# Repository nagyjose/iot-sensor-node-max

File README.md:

# IoT Sensor Node Max (`iot-sensor-node-max`)

> Full-featured wireless IoT environmental & telemetry node based on the Raspberry Pi Pico W, equipped with dual 18650 Li-Ion batteries, independent dual-channel charging & protection, zero-quiescent voltage sensing, multiple sensor interfaces, rich expansion ports (dual I2C, dual SPI, analog ADC), and complete production-ready CAM Gerber data.

**Project Status:** Completed & Functional | **Technologies:** Autodesk Eagle, Hardware PCB Design, RP2040 / Pico W, RS-274X Gerbers, MicroPython / C++

---

## 1. Overview & Key Features

The **IoT Sensor Node Max** is the high-capacity, expandable flagship hardware revision in the Raspberry Pi Pico W sensor node family. Designed for remote deployments where long battery autonomy and extensive sensor connectivity are vital, it doubles the battery capacity with two 18650 cells, provides independent per-cell safety and charging circuits, and breaks out dual I2C, dual SPI, analog ADC, and multi-purpose GPIO expansion headers.

### Key Highlights
- **Microcontroller:** Raspberry Pi Pico W socket (RP2040 dual-core ARM Cortex-M0+ up to 133 MHz, 264 KB SRAM, 2 MB Flash, onboard 2.4 GHz 802.11n Wi-Fi and BLE 5.2).
- **Dual-Cell Power Architecture:**
  - Dual 18650 Li-Ion battery holders (`BAT1` & `BAT2`) with parallel power path configuration for doubled battery operating life.
  - **Dual Microchip MCP73831T** linear Li-Ion charge controllers (`U1`, `U3`) with independent charging status LEDs (`D1`, `D2`), charging both cells in parallel via USB VBUS.
  - **Dual Diodes Inc. AP9101C** dedicated protection ICs (`U2`, `U4`) paired with dual **BXT280N02B** N-MOSFETs (`M1`, `M2`) providing independent overcharge, overdischarge cutoff, and short-circuit protection for each individual cell.
  - **Triple Power Path Switch:** Schottky diode array (`STPS1L30`) and P-channel power MOSFET (`YJL2301D`, `M3`) for seamless automatic handover between external USB 5 V and battery rails.
- **Dual-Channel Precision Battery Monitoring:**
  - **LM4040** precision shunt voltage reference tied to RP2040 `ADC_REF`.
  - Independent switched resistor dividers for each battery cell:
    - Cell 1: Switched by GP3 (`EN-MEAS-1`) via MOSFETs `M4` & `M6` into `VADC-1` (`GP27`).
    - Cell 2: Switched by GP2 (`EN-MEAS-0`) via MOSFETs `M4` & `M5` into `VADC-2` (`GP28`).
  - Zero quiescent current draw through measurement dividers during sleep mode.
  - Diode clamping protection (`RB751V40T1G`) across all ADC inputs.
- **Integrated Sensors & Displays:**
  - **AM2302 (DHT22):** Relative humidity and ambient temperature digital sensor on `GP14`.
  - **DS18B20:** 1-Wire precision digital temperature sensor on `GP15`.
  - **OLED Display Header:** 4-pin socket for 0.96" or 1.3" I2C OLED displays (SSD1306 / SH1106) on `I2C0` (`GP4` / `GP5`).
  - **nRF24L01+ 2.4 GHz RF Header:** SPI socket for Nordic nRF24L01+ wireless transceiver module on `SPI0` (`GP16`–`GP20`).
- **Rich Expansion Connectors:**
  - **Dual I2C Connectors (`CON3`, `CON4`):** 4-pin headers for external I2C sensor daisy chains (BME280, SHT31, INA219, etc.).
  - **Dual SPI Connectors (`CON5`, `CON6`):** 5-pin headers with dedicated independent Chip Selects `CSN-1` (`GP21`) and `CSN-2` (`GP22`).
  - **External Analog Input (`CON1`):** 3-pin connector (VCC, GND, SIG) on `GP26` with Schottky overvoltage clamping for analog sensors.
  - **S2G6 Jumper / Breakout (`CON7`):** Multi-purpose configuration jumper matrix breaking out digital GPIOs `GP6`–`GP13`.
- **Complete Manufacturing Package:** Includes verified RS-274X Gerbers, NC drill files, automated Pick & Place (PnP) centroid files, and pre-packaged ZIP archives ready for PCB manufacturing (JLCPCB, PCBWay).

---

## 2. Architecture & Block Diagram

```mermaid
flowchart TD
    subgraph PowerSystem["⚡ Dual Battery Power & Protection System"]
        USB["USB 5V (VBUS)"] --> CHG1["MCP73831T Charger 1<br/>+ LED D1"]
        USB --> CHG2["MCP73831T Charger 2<br/>+ LED D2"]
        USB --> PATH["Power Path Switch<br/>(P-MOS M3 & D3)"]
        BAT1["18650 Battery Cell 1"] --> PROT1["AP9101C + Dual NMOS M1<br/>Protection Circuit"]
        BAT2["18650 Battery Cell 2"] --> PROT2["AP9101C + Dual NMOS M2<br/>Protection Circuit"]
        CHG1 --> PROT1
        CHG2 --> PROT2
        PROT1 -->|D4 Schottky| PATH
        PROT2 -->|D5 Schottky| PATH
        PATH --> VSYS["VSYS (System Rail)"]
        VSYS --> PICO_REG["Pico W RT6154<br/>Buck-Boost Converter"]
        PICO_REG --> 3V3["3.3V Power Rail"]
    end

    subgraph DualMonitoring["🔋 Independent Battery Telemetry"]
        PROT1 -->|VBATT-1| DIV1["Switched Divider 1<br/>(8.2k / 22k)"]
        PROT2 -->|VBATT-2| DIV2["Switched Divider 2<br/>(8.2k / 22k)"]
        MCU -->|GP3: EN-MEAS-1| GATE1["MOSFET Gate M4 / M6"]
        MCU -->|GP2: EN-MEAS-0| GATE2["MOSFET Gate M4 / M5"]
        GATE1 --> DIV1
        GATE2 --> DIV2
        DIV1 -->|VADC-1| ADC1["ADC1 (GP27) - Cell 1"]
        DIV2 -->|VADC-2| ADC2["ADC2 (GP28) - Cell 2"]
        VREF["LM4040 Precision Ref"] -->|ADC_REF| PICO
    end

    subgraph MCU["🧠 Processing & Core Connectivity"]
        PICO["Raspberry Pi Pico W<br/>(RP2040 MCU)"]
        WIFI["Onboard CYW43439<br/>Wi-Fi 802.11n & BLE 5.2"]
    end

    subgraph IntegratedPeripherals["📡 Onboard Sensors & Radio"]
        DHT["AM2302 / DHT22<br/>(Humidity & Temp)"] ---|GP14| MCU
        DS["DS18B20<br/>(1-Wire Temp)"] ---|GP15| MCU
        OLED["OLED Display<br/>(SSD1306 / SH1106)"] ---|I2C0: GP4/GP5| MCU
        NRF["nRF24L01+ Module<br/>(2.4 GHz RF)"] ---|SPI0: GP16-GP20| MCU
    end

    subgraph ExpansionBuses["🔌 Expansion Ports"]
        I2C_EXT["Dual I2C Expansion<br/>(CON3 & CON4)"] ---|I2C0 Bus| MCU
        SPI_EXT["Dual SPI Expansion<br/>(CON5: CS1 / CON6: CS2)"] ---|SPI0 + GP21/GP22| MCU
        ADC_EXT["External ADC Sensor<br/>(CON1 - Protected)"] ---|GP26: VADC-0| MCU
        JUMP["Jumper / GPIO Breakout<br/>(CON7: S2G6)"] ---|GP6-GP13| MCU
    end

    3V3 --> MCU
    3V3 --> IntegratedPeripherals
    3V3 --> ExpansionBuses
```

---

## 3. Schematic & Circuit Diagram

📄 [Open original high-resolution schematic (PDF)](Sensor-node_max.pdf)

---

## 4. Hardware Specifications & Pin Mapping

### Complete Pico W Pinout

| Pico W Pin | Eagle Net Name | Hardware Function / Connected Device | Notes |
| :--- | :--- | :--- | :--- |
| **GP0** | `UART0-TX` | Serial UART TX | Debug / serial telemetry |
| **GP1** | `UART0-RX` | Serial UART RX | Debug / serial telemetry |
| **GP2** | `EN-MEAS-0` | Battery 2 measurement enable | Gates M4 & M5 MOSFETs |
| **GP3** | `EN-MEAS-1` | Battery 1 measurement enable | Gates M4 & M6 MOSFETs |
| **GP4** | `I2C0-SDA` | I2C Data bus | Connected to OLED, CON3, CON4 (pull-up R15) |
| **GP5** | `I2C0-SCK` | I2C Clock bus | Connected to OLED, CON3, CON4 (pull-up R16) |
| **GP6–GP9** | `GPIO-2`..`GPIO-5`| Digital GPIO pins | Broken out on CON7 jumper block |
| **GP10–GP13**| `GPIO-6`..`GPIO-9`| Digital GPIO pins | Broken out on CON7 jumper block |
| **GP14** | `AM2302-DATA` | AM2302 / DHT22 Data | Onboard relative humidity / temperature |
| **GP15** | `1-WIRE-DQ` | DS18B20 1-Wire Data | Onboard digital temperature probe |
| **GP16** | `SPI0-MISO` | SPI0 MISO | nRF24L01+ socket & CON5, CON6 expansion |
| **GP17** | `SPI0-CSN` | nRF24L01+ Chip Select | Dedicated SPI0 CSN for RF module |
| **GP18** | `SPI0-SCK` | SPI0 Clock | nRF24L01+ socket & CON5, CON6 expansion |
| **GP19** | `SPI0-MOSI` | SPI0 MOSI | nRF24L01+ socket & CON5, CON6 expansion |
| **GP20** | `RADIO-EN` | nRF24L01+ Chip Enable (CE) | Radio TX/RX enable |
| **GP21** | `CSN-1` | Expansion SPI 1 Chip Select | Dedicated CS for CON5 expansion header |
| **GP22** | `CSN-2` | Expansion SPI 2 Chip Select | Dedicated CS for CON6 expansion header |
| **GP26** | `VADC-0` | Analog ADC Channel 0 | External analog input (CON1), diode protected |
| **GP27** | `VADC-1` | Analog ADC Channel 1 | Switched battery 1 voltage measurement |
| **GP28** | `VADC-2` | Analog ADC Channel 2 | Switched battery 2 voltage measurement |
| **ADC_REF** | `ADC-REF` | Reference Voltage | Tied to LM4040 precision shunt reference |

### Expansion Connectors Pinout

- **`CON1` (External ADC):** Pin 1 = `3V3`, Pin 2 = `VADC-0` (analog in with Schottky protection), Pin 3 = `GND`.
- **`CON3` & `CON4` (Dual I2C):** Pin 1 = `3V3`, Pin 2 = `GND`, Pin 3 = `I2C0-SCK`, Pin 4 = `I2C0-SDA`.
- **`CON5` (SPI Expansion 1):** Pin 1 = `3V3`, Pin 2 = `GND`, Pin 3 = `SPI0-SCK`, Pin 4 = `SPI0-MOSI`, Pin 5 = `SPI0-MISO`, Pin 6 = `CSN-1` (`GP21`).
- **`CON6` (SPI Expansion 2):** Pin 1 = `3V3`, Pin 2 = `GND`, Pin 3 = `SPI0-SCK`, Pin 4 = `SPI0-MOSI`, Pin 5 = `SPI0-MISO`, Pin 6 = `CSN-2` (`GP22`).
- **`CON7` (S2G6 Jumper):** Configurable jumper links for matrix routing between GP6–GP9 and GP10–GP13.

---

## 5. PCB Layout & Manufacturing Specifications

- **PCB Dimensions:** 78.79 mm × 54.56 mm (3.10" × 2.15")
- **Layer Count:** 2 layers (Top Copper, Bottom Copper)
- **Minimum Trace / Clearance:** 0.25 mm / 0.25 mm (10 mil / 10 mil)
- **Board Outline:** Chamfered corners with mounting holes for standardized enclosures.
- **Top Side:** Raspberry Pi Pico W module, OLED display header, nRF24L01+ socket, sensor headers, expansion ports (CON1–CON7).
- **Bottom Side:** Dual 18650 battery spring clips (`BAT1`, `BAT2`), dual chargers, and protection ICs.

### Manufacturing Files (`CAMOutputs/`)

| Directory / File | Format | Description |
| :--- | :--- | :--- |
| `CAMOutputs/GerberFiles/copper_top.gbr` | RS-274X | Layer 1 Top Copper |
| `CAMOutputs/GerberFiles/copper_bottom.gbr`| RS-274X | Layer 16 Bottom Copper |
| `CAMOutputs/GerberFiles/soldermask_top.gbr` | RS-274X | Top Soldermask |
| `CAMOutputs/GerberFiles/soldermask_bottom.gbr`| RS-274X | Bottom Soldermask |
| `CAMOutputs/GerberFiles/silkscreen_top.gbr` | RS-274X | Top Silkscreen Legend |
| `CAMOutputs/GerberFiles/silkscreen_bottom.gbr`| RS-274X | Bottom Silkscreen Legend |
| `CAMOutputs/GerberFiles/profile.gbr` | RS-274X | Board Edge Outline / Milling |
| `CAMOutputs/DrillFiles/drill_1_16.xln` | Excellon NC | Plated and Non-Plated Through Holes |
| `CAMOutputs/Assembly/PnP_Sensor-node_max_*.txt` | Text Centroid | Pick & Place automated component positions |
| `Sensor-node_max_2025-07-29.zip` | ZIP Archive | Complete ready-to-order Gerber package |

---

## 6. Repository Structure

```text
.
├── docs/
│   └── images/
│       └── schematic.png   # High-resolution schematic preview (180 DPI)
├── CAMOutputs/
│   ├── Assembly/           # Automated Pick & Place and BOM files
│   ├── DrillFiles/         # Excellon NC drill files
│   └── GerberFiles/        # RS-274X fabrication photoplot files
├── Sensor-node_max.sch     # Autodesk Eagle schematic
├── Sensor-node_max.brd     # Autodesk Eagle PCB layout
├── Sensor-node_max.pdf     # High-resolution schematic and layout drawing export
├── Sensor-node_max.cam     # CAM processor job file
├── Sensor-node_max.dru     # Design rules specification (DRC)
├── Sensor-node_max.scr     # Eagle layer script
├── Sensor-node_max_*.zip   # Pre-packaged Gerber archives for manufacturing
├── .gitignore              # Eagle & OS backup filter
└── README.md               # Project documentation
```

---

## 7. How to Use & Firmware Deployment

### MicroPython Dual-Battery Reading Example

The following snippet demonstrates reading both independent battery voltages while ensuring zero power waste during deep sleep:

```python
from machine import Pin, ADC
import time

en_meas_1 = Pin(3, Pin.OUT)  # Cell 1 measurement gate
en_meas_0 = Pin(2, Pin.OUT)  # Cell 2 measurement gate
adc_1 = ADC(Pin(27))         # Cell 1 ADC (GP27)
adc_2 = ADC(Pin(28))         # Cell 2 ADC (GP28)

def read_battery_voltages():
    # Measure Cell 1
    en_meas_1.value(1)
    time.sleep_us(50)
    raw1 = adc_1.read_u16()
    en_meas_1.value(0)

    # Measure Cell 2
    en_meas_0.value(1)
    time.sleep_us(50)
    raw2 = adc_2.read_u16()
    en_meas_0.value(0)

    # Convert using 8.2k / 22k divider ratio and 3.3V reference
    ratio = (8.2 + 22.0) / 22.0
    v1 = (raw1 / 65535.0) * 3.3 * ratio
    v2 = (raw2 / 65535.0) * 3.3 * ratio
    return v1, v2

v_cell1, v_cell2 = read_battery_voltages()
print(f"Battery 1: {v_cell1:.2f} V | Battery 2: {v_cell2:.2f} V")
```

---

## 8. Relations & Ecosystem Links

This project is part of a modular IoT sensor ecosystem:
- **[`iot-sensor-node-med`](https://github.com/nagyjose/iot-sensor-node-med):** Compact single-cell sibling node for constrained enclosures.
- **[`pico-w-iot-nodes`](https://github.com/nagyjose/pico-w-iot-nodes):** MicroPython firmware repository providing BLE GATT service, MQTT telemetry, sensor reading drivers, and power management loops.
- **[`ble-sensor-gui`](https://github.com/nagyjose/ble-sensor-gui):** PyQt5 / QML cross-platform telemetry monitoring dashboard.

---

## 9. License & Author

- **Author:** Josef Nagy (`nagyjose`)
- **Design Tool:** Autodesk Eagle v9.x
- **License:** Open Hardware / MIT License

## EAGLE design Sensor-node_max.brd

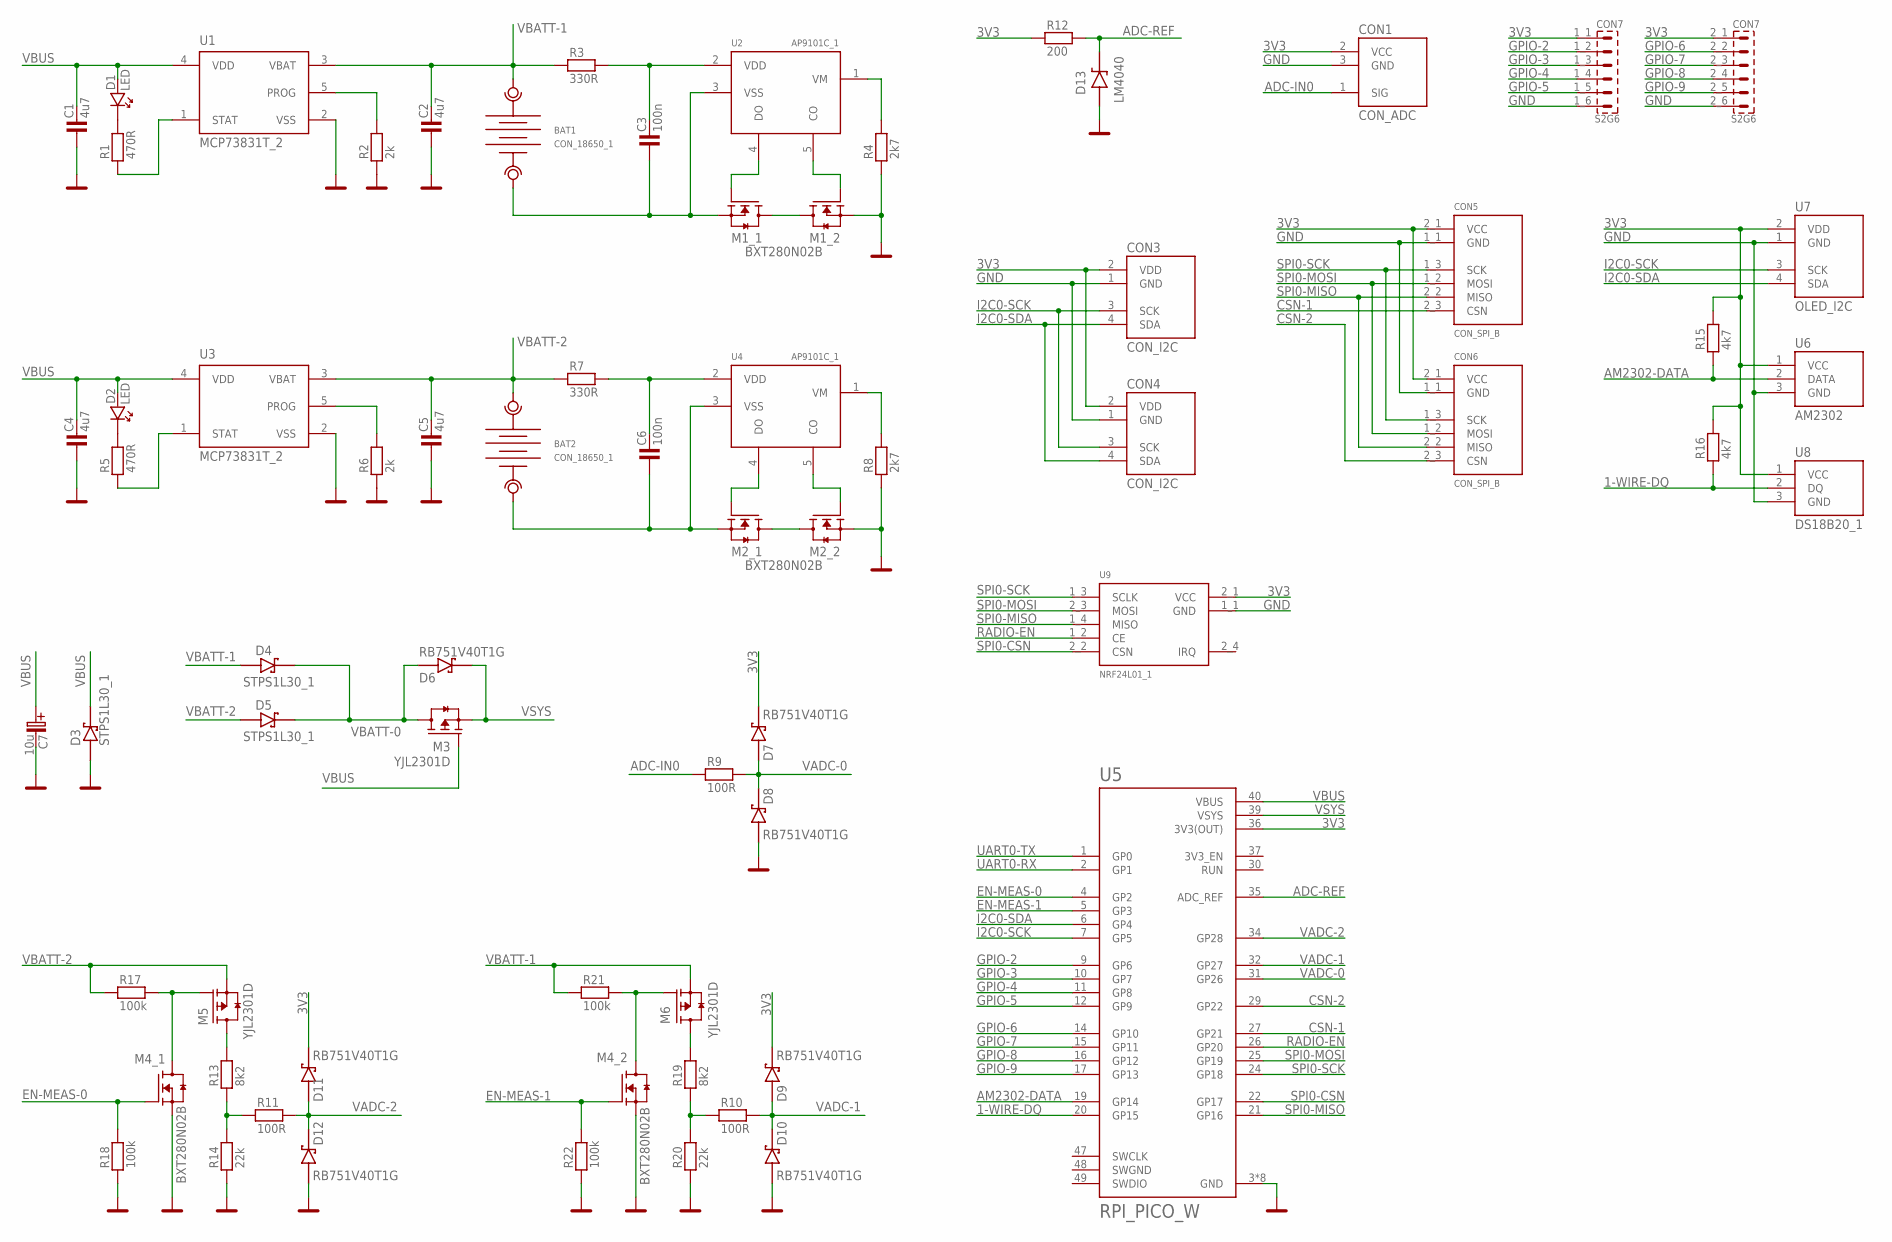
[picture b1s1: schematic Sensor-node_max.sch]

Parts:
BAT1, BAT2: CON_18650_1; BATTERY_PADS_1
C1, C2, C4, C5: 4u7; 0805
C3, C6: 100n; 0805
C7: 10u; C_EL-SMD_D
CON1: CON_ADC; ADC_CON
CON3, CON4: CON_I2C; I2C_CONN
CON5, CON6: CON_SPI_B; SPI_CONN_2
CON7: S2G6; S2G6_JUM
D1, D2: LED; P1206
D3, D4, D5: STPS1L30_1; SMA
D6, D7, D8, D9, D10, D11, D12: RB751V40T1G; SOD323
D13: LM4040; TRANSISTOR-FET_SOT23
M1, M2, M4: BXT280N02B; SO8
M3, M5, M6: YJL2301D; TRANSISTOR-FET_SOT23
R1, R5: 470R; 0805
R2, R6: 2k; 0805
R3, R7: 330R; 0805
R4, R8: 2k7; 0805
R9, R10, R11: 100R; 0805
R12: 200; 0805
R13, R19: 8k2; 0805
R14, R20: 22k; 0805
R15, R16: 4k7; 0805
R17, R18, R21, R22: 100k; 0805
U1, U3: MCP73831T_2; GHI-IC_SOT23-5(MICROCHIP)
U2, U4: AP9101C_1; GHI-IC_SOT23-5(MICROCHIP)
U5: RPI_PICO_W
U6: AM2302
U7: OLED_I2C; I2C_CONN
U8: DS18B20_1; DS18B20_CABLE
U9: NRF24L01_1; NRF24L01_NORM

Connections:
1-WIRE-DQ: R16.1, U5.20 (GP15), U8.2 (DQ)
3V3: CON1.2 (VCC), CON3.2 (VDD), CON4.2 (VDD), CON5.2_1 (VCC), CON6.2_1 (VCC), CON7.1_1 (1), CON7.2_1 (1), D7.1 (C), D9.1 (C), D11.1 (C), R12.1, R15.2, R16.2, U5.36 (3V3(OUT)), U6.1 (VCC), U7.2 (VDD), U8.1 (VCC), U9.2_1 (VCC)
ADC-IN0: CON1.1 (SIG), R9.1
ADC-IN2: R11.1, R13.1, R14.2
ADC-REF: D13.1 (C), R12.2, U5.35 (ADC_REF)
AM2302-DATA: R15.1, U5.19 (GP14), U6.2 (DATA)
CO1: M1.2 (G), U2.5 (CO)
CO2: M2.2 (G), U4.5 (CO)
CSN-1: CON5.2_3 (CSN), U5.27 (GP21)
CSN-2: CON6.2_3 (CSN), U5.29 (GP22)
DO1: M1.4 (G), U2.4 (DO)
DO2: M2.4 (G), U4.4 (DO)
EN-MEAS-0: M4.4 (G), R18.2, U5.4 (GP2)
EN-MEAS-1: M4.2 (G), R22.2, U5.5 (GP3)
GND: C1.1, C2.1, C4.1, C5.1, C7.- (C_EL-), CON1.3 (GND), CON3.1 (GND), CON4.1 (GND), CON5.1_1 (GND), CON6.1_1 (GND), CON7.1_6 (6), CON7.2_6 (6), D3.2 (A), D8.2 (A), D10.2 (A), D12.2 (A), D13.2 (A), M1.1 (S), M2.1 (S), M4.1 (S), M4.3 (S), R2.1, R4.1, R6.1, R8.1, R14.1, R18.1, R20.1, R22.1, U1.2 (VSS), U3.2 (VSS), U5.3 (GND), U5.8 (GND), U5.13 (GND), U5.18 (GND), U5.23 (GND), U5.28 (GND), U5.33 (GND), U5.38 (GND), U6.3 (GND), U7.1 (GND), U8.3 (GND), U9.1_1 (GND)
GPIO-2: CON7.1_2 (2), U5.9 (GP6)
GPIO-3: CON7.1_3 (3), U5.10 (GP7)
GPIO-4: CON7.1_4 (4), U5.11 (GP8)
GPIO-5: CON7.1_5 (5), U5.12 (GP9)
GPIO-6: CON7.2_2 (2), U5.14 (GP10)
GPIO-7: CON7.2_3 (3), U5.15 (GP11)
GPIO-8: CON7.2_4 (4), U5.16 (GP12)
GPIO-9: CON7.2_5 (5), U5.17 (GP13)
I2C0-SCK: CON3.3 (SCK), CON4.3 (SCK), U5.7 (GP5), U7.3 (SCK)
I2C0-SDA: CON3.4 (SDA), CON4.4 (SDA), U5.6 (GP4), U7.4 (SDA)
unnamed: D1.K, R1.2
unnamed: M4.7 (D), M4.8 (D), M6.1 (G), R21.2
unnamed: M6.3 (D), R19.2
unnamed: R10.1, R19.1, R20.2
unnamed: D2.K, R5.2
unnamed: M4.5 (D), M4.6 (D), M5.1 (G), R17.2
unnamed: M5.3 (D), R13.2
NMOS-CONN-1: M1.5 (D), M1.6 (D), M1.7 (D), M1.8 (D)
NMOS-CONN-2: M2.5 (D), M2.6 (D), M2.7 (D), M2.8 (D)
P1-: BAT1.GND_1 (GND), BAT1.GND_2 (GND), C3.1, M1.3 (S), U2.3 (VSS)
P2-: BAT2.GND_1 (GND), BAT2.GND_2 (GND), C6.1, M2.3 (S), U4.3 (VSS)
PROG1: R2.2, U1.5 (PROG)
PROG2: R6.2, U3.5 (PROG)
RADIO-EN: U5.26 (GP20), U9.1_2 (CE)
SPI0-CSN: U5.22 (GP17), U9.2_2 (CSN)
SPI0-MISO: CON5.2_2 (MISO), CON6.2_2 (MISO), U5.21 (GP16), U9.1_4 (MISO)
SPI0-MOSI: CON5.1_2 (MOSI), CON6.1_2 (MOSI), U5.25 (GP19), U9.2_3 (MOSI)
SPI0-SCK: CON5.1_3 (SCK), CON6.1_3 (SCK), U5.24 (GP18), U9.1_3 (SCLK)
STAT1: R1.1, U1.1 (STAT)
STAT2: R5.1, U3.1 (STAT)
SWGND: U5.48 (SWGND)
UART0-RX: U5.2 (GP1)
UART0-TX: U5.1 (GP0)
VADC-0: D7.2 (A), D8.1 (C), R9.2, U5.31 (GP26)
VADC-1: D9.2 (A), D10.1 (C), R10.2, U5.32 (GP27)
VADC-2: D11.2 (A), D12.1 (C), R11.2, U5.34 (GP28)
VBATT-0: D4.1 (C), D5.1 (C), D6.2 (A), M3.3 (D)
VBATT-1: BAT1.UCC_1 (UCC), BAT1.UCC_2 (UCC), C2.2, D4.2 (A), M6.2 (S), R3.1, R21.1, U1.3 (VBAT)
VBATT-2: BAT2.UCC_1 (UCC), BAT2.UCC_2 (UCC), C5.2, D5.2 (A), M5.2 (S), R7.1, R17.1, U3.3 (VBAT)
VBUS: C1.2, C4.2, C7.+ (C_EL+), D1.A, D2.A, D3.1 (C), M3.1 (G), U1.4 (VDD), U3.4 (VDD), U5.40 (VBUS)
VDD-AP9101-1: C3.2, R3.2, U2.2 (VDD)
VDD-AP9101-2: C6.2, R7.2, U4.2 (VDD)
VM1: R4.2, U2.1 (VM)
VM2: R8.2, U4.1 (VM)
VSYS: D6.1 (C), M3.2 (S), U5.39 (VSYS)

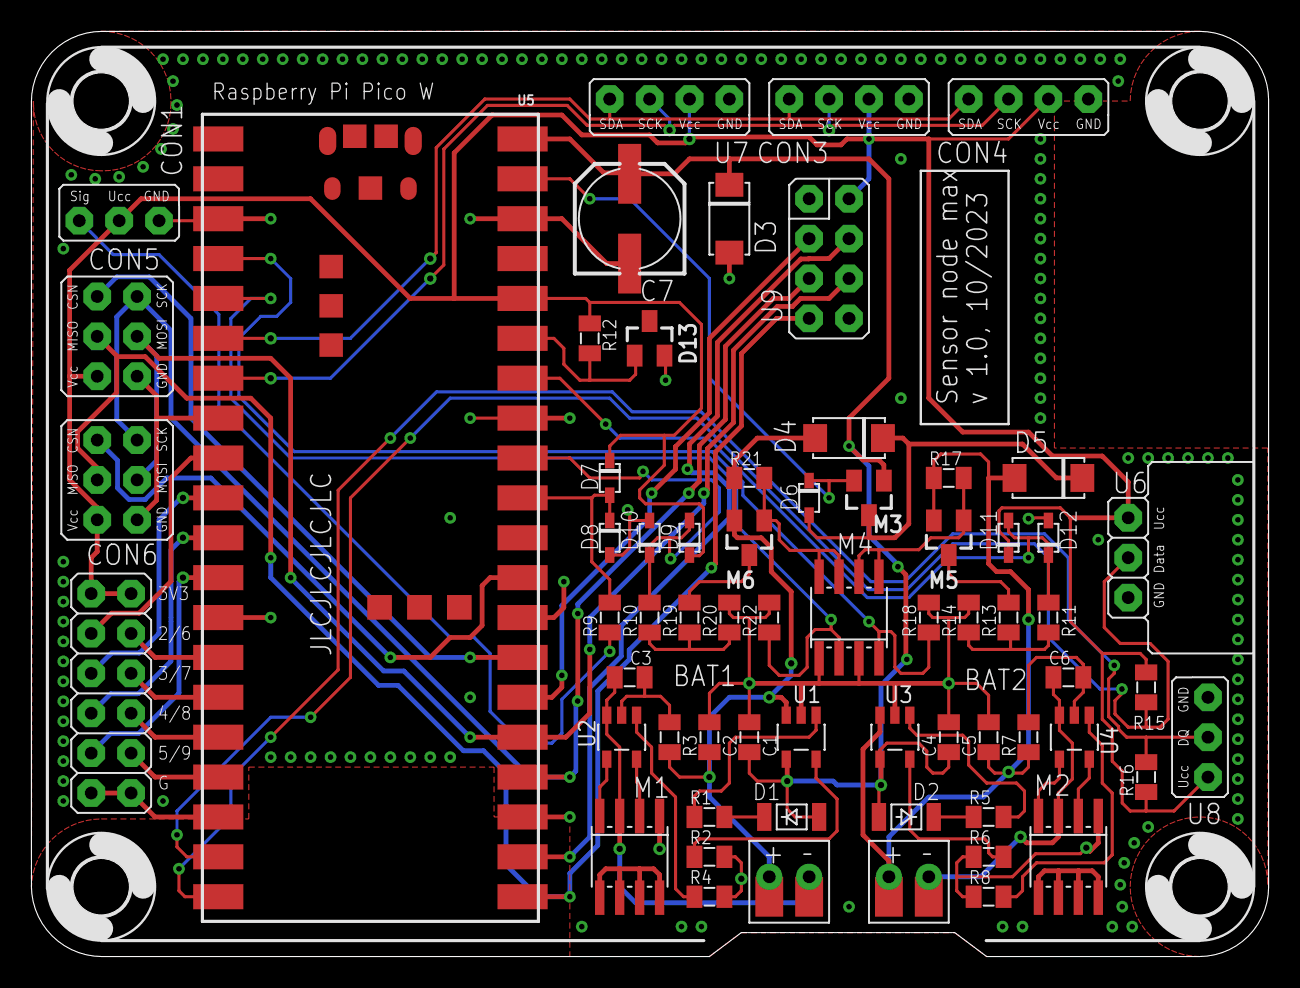
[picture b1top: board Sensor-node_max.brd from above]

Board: 2 copper layers, 78.8 x 58.9 mm, 69 parts (0 on the bottom side), 57 nets.

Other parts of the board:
U$1, U$2, U$3, U$4: 3,6

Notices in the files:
parts and their libraries:
Copyright (C) PaJa 2011-2014
Copyright (C) PaJa 2001-2014
